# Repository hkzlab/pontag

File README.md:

# PONTAG
## Introduction
PONTAG is a board that converts a PS/2 mouse into a serial mouse that can be used on old IBM PC and clones, which lacked PS/2 ports but had plenty of serial interfaces (especially if expansion cards are installed).

## Features & Limitations
* Supports 3 buttons+wheel PS/2 mouses and converts their protocol to RS232 serial usable on old PC systems.
* The board requires an external power supply between 8V and 12V to power the MCU and mouse
* Detects PS/2 mouses with wheel and without and notifies the user via LED (5 fast blinks for a normal mouse, 20 fast blinks for a mouse with wheel)
* Can be configured for various resolutions and mouse protocols by pushing mouse buttons

### Configuration
The board can be configured during powerup by pressing the mouse keys. The configuration will be retained for all subsequent boots.
To configure the board you must keep the mouse button pressed during a reset/bootup. A sequence of **15 slow blinks** will notify the user of the accepted command, then the board will be reset with the new configuration.

* **Left mouse button pressed**: Switches between simple Microsoft protocol and Microsoft protocol with wheel (**DEFAULT:** MS+Wheel)
* **Right mouse button pressed**: Switches mouse resolution, switching between 1, 2, 4 or 8 counts per mm traveled (**DEFAULT:** 4 counts per mm)
* **Both buttons pressed**: Resets the board to defaults

### Extra Header
The board supports some special options that can be toggled via external header, shorting the corrisponding pin to GND.

* **Pin 1**: The board will enter debug mode, and start printing debug strings on the serial port. It will NOT work as a mouse.
* **Pin 2**: If jumpered, the board enter power save mode after 3 minutes of mouse inactivity.
* **Pin 3**: If shorted, forces the use of the simple Microsoft protocol (2 buttons, no wheel), regardless of what is stored in the EEPROM.
* **Pin 4**: If jumpered, the board will skip the PS/2 intellimouse wheel activation sequence. (**not exposed on board 1.0 !!!**)

## Supported protocols
PONTAG emulates a Microsoft 3-buttons Wheel serial mouse by default and transmits the `0x4D 0x5A 0x40 0x00 0x00 0x00` detection string when RTS signal is toggled.

The boards are tested with [CuteMouse](http://cutemouse.sourceforge.net/).

## Credits

- Some footprints are taken from [4x1md](https://github.com/4x1md/kicad_libraries)
- Took and modified PS/2 code from [sensi.org](http://sensi.org/~svo/%5Bm%5Douse/) and [mouse1351](https://github.com/svofski/mouse1351)

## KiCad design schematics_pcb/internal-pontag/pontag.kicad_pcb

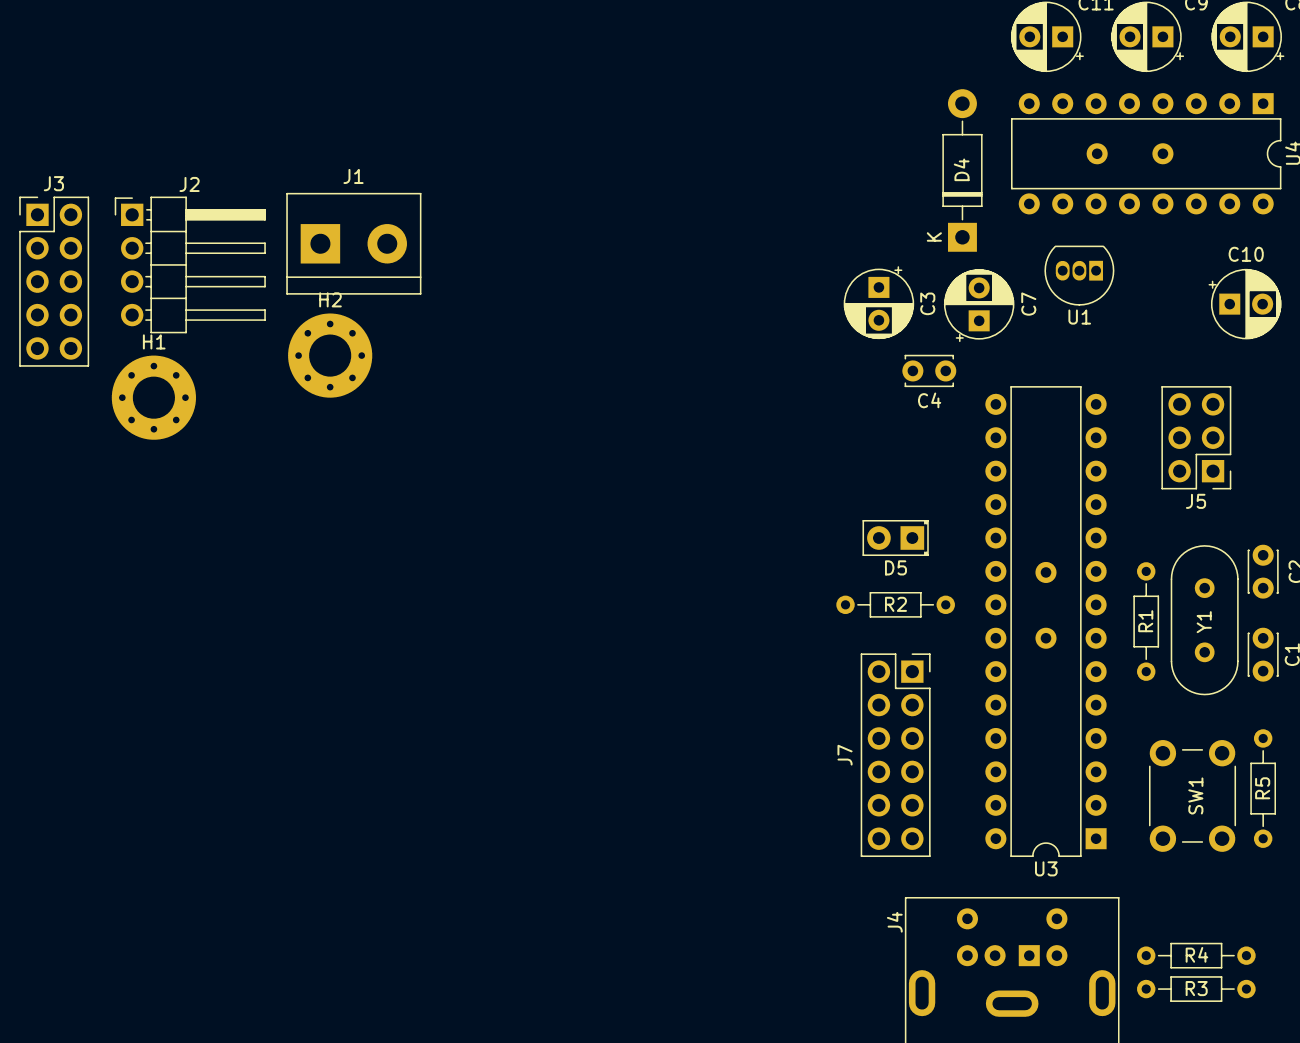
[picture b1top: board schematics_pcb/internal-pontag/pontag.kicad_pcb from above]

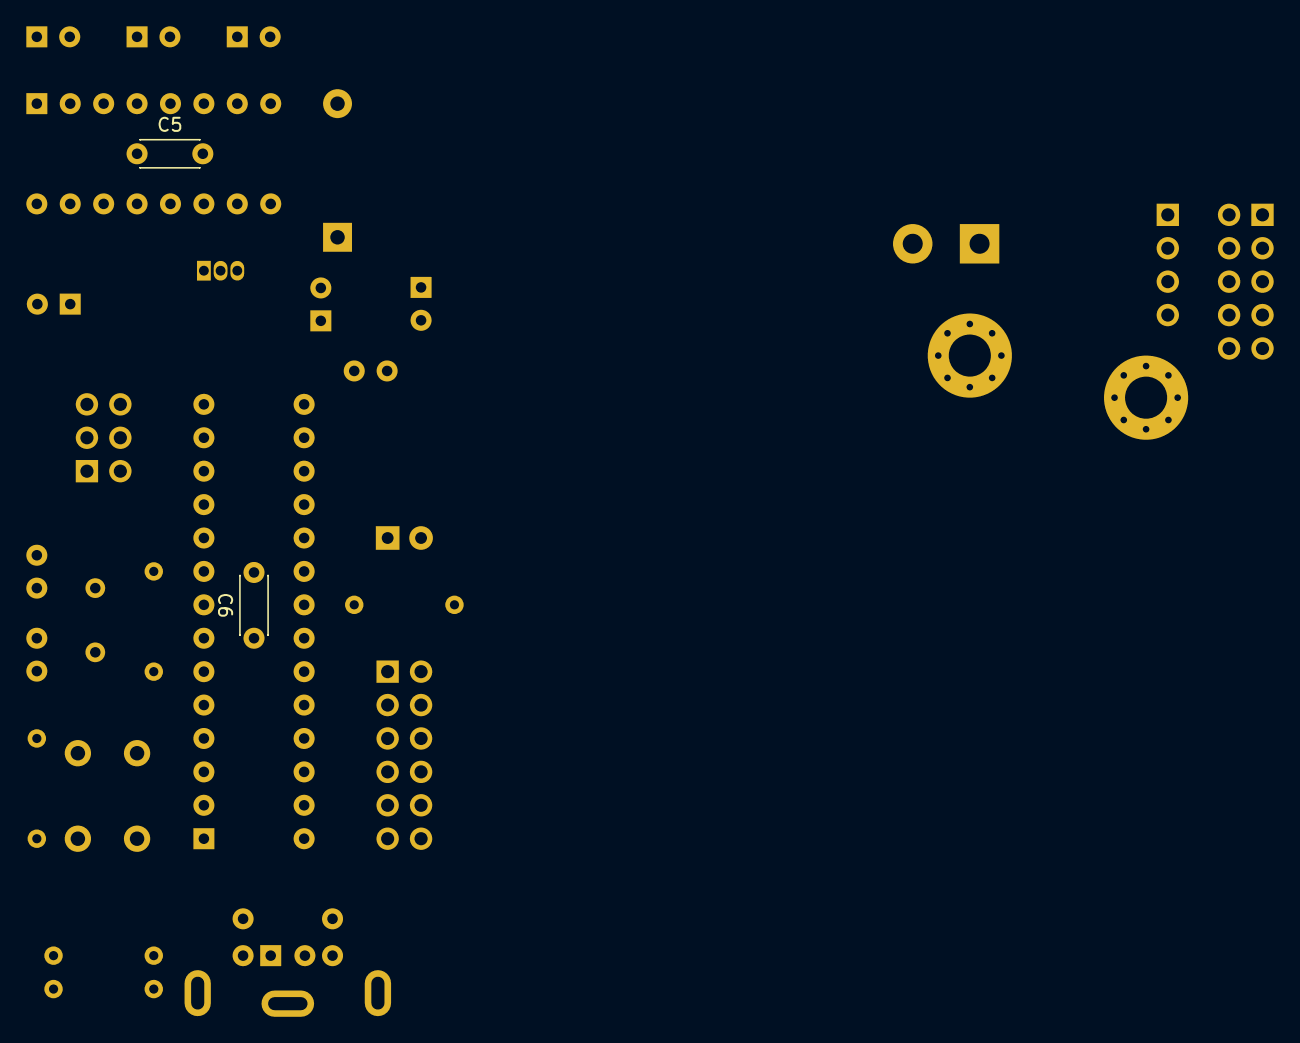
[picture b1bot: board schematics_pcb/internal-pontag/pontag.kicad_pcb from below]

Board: 2 copper layers, 31 parts (2 on the bottom side), 31 nets, no tracks yet.

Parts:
C1, C2: 22pF; C_Disc_D3.0mm_W2.0mm_P2.50mm
C3, C7, C8, C9, C10, C11: 1.0uF; CP_Radial_D5.0mm_P2.50mm
C4: 10nF; C_Disc_D3.4mm_W2.1mm_P2.50mm
C5, C6: 100nF; C_Disc_D4.3mm_W1.9mm_P5.00mm
D4: 1N4001; D_DO-41_SOD81_P10.16mm_Horizontal
D5: LED; LED_D2.0mm_W4.8mm_H2.5mm_FlatTop
H1, H2: MountingHole_Pad; MountingHole_3.2mm_M3_Pad_Via
J1: PWR Connector; TerminalBlock_bornier-2_P5.08mm
J2: Floppy PWR Connector; PinHeader_1x04_P2.54mm_Horizontal
J3: RS232 Port; PinHeader_2x05_P2.54mm_Vertical
J4: PS/2 Mouse; Connector_Mini-DIN_Female_6Pin_2rows
J5: AVR-ISP-6; PinHeader_2x03_P2.54mm_Vertical
J7: Extra; PinSocket_2x06_P2.54mm_Vertical
R1: 1M; R_Axial_DIN0204_L3.6mm_D1.6mm_P7.62mm_Horizontal
R2: 470; R_Axial_DIN0204_L3.6mm_D1.6mm_P7.62mm_Horizontal
R3, R4: 5K; R_Axial_DIN0204_L3.6mm_D1.6mm_P7.62mm_Horizontal
R5: 10K; R_Axial_DIN0204_L3.6mm_D1.6mm_P7.62mm_Horizontal
SW1: Reset; SW_PUSH_6mm
U1: L78L05_TO92; TO-92_Inline
U3: ATmega328P-PU; DIP-28_W7.62mm
U4: MAX232; DIP-16_W7.62mm
Y1: 8.0Mhz; Crystal_HC49-U_Vertical

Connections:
+12V: C3.1, D4.1, U1.3
/MISO: J5.1, U3.18
/MOSI: J5.4, U3.17
/PS2-CLOCK: J4.5, R4.2, U3.4
/PS2-DATA: J4.1, R3.2, U3.6
/RESET: J5.5, R5.1, SW1.2, U3.1
/RS232-RTS: J3.7, U4.13
/RS232-RX: J3.2, U4.7
/RS232-TX: J3.3, U4.8
/SCK: D5.2, J5.3, U3.19
/TTL-CTS: U3.5, U4.12
/TTL-RX: U3.2, U4.9
/TTL-TX: U3.3, U4.10
/XTAL1: C1.2, R1.1, U3.9, Y1.2
/XTAL2: C2.2, R1.2, U3.10, Y1.1
GND: C1.1, C2.1, C3.2, C4.2, C5.2, C6.2, C7.2, C11.1, H1.1, H2.1, J1.2, J2.2, J2.3, J3.5, J4.3, J4.7, J5.6, J7.2, J7.4, J7.6, J7.8, J7.10, J7.12, R2.2, SW1.1, U1.2, U3.8, U3.22, U4.11, U4.15
unnamed: C8.1, U4.1
unnamed: C8.2, U4.3
unnamed: C9.1, U4.4
unnamed: C9.2, U4.5
unnamed: C10.1, U4.2
unnamed: C11.2, U4.6
unnamed: D4.2, J1.1, J2.4
unnamed: D5.1, R2.1
unnamed: J7.1, U3.23
unnamed: J7.3, U3.24
unnamed: J7.5, U3.25
unnamed: J7.7, U3.26
unnamed: J7.9, U3.27
unnamed: J7.11, U3.28
VCC: C4.1, C5.1, C6.1, C7.1, C10.2, J4.4, J5.2, R3.1, R4.1, R5.2, U1.1, U3.7, U3.20, U3.21, U4.16

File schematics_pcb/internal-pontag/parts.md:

# Pontag proto 00
## Parts list
### ICs
- U1 - 78L05 TO92 regulator
- U3 - ATMega328P
- U4 - MAX232

### Resistors
- R1 - 1M ohm resistor
- R2 - 470 ohm resistor
- R3,R4 - 5K ohm resistors
- R5 - 10K ohm resistors

### Capacitors
- C1,C2 - 22pF disc ceramic capacitors
- C3,C8-C11 - 1.0uF/25V electrolytic capacitors
- C4 - 10nF ceramic capacitor
- C5,C6 - 100nF ceramic capacitors
- C7 - 1.0uF ceramic capacitor

### Diodes
- D1-D3 - 1n4148 silicon diodes
- D4 - 1n4001 diode
- D5 - LED

### Headers & Connectors
- J1 - 02x02 2.54mm header
- J2 - 01x02 2.54mm header
- J3 - DB9 female connector
- J4 - 6pin Mini-din female connector
- J5 - 02x03 2.54mm header
- J6 - 01x02 2.54mm header
- J7 - 02x06 2.54mm header
- JP1 - 01x02 2.54mm header
- JP2 - 01x02 2.54mm header

### Misc
- SW1 - 4pin push button
- Y1 - 8Mhz crystal

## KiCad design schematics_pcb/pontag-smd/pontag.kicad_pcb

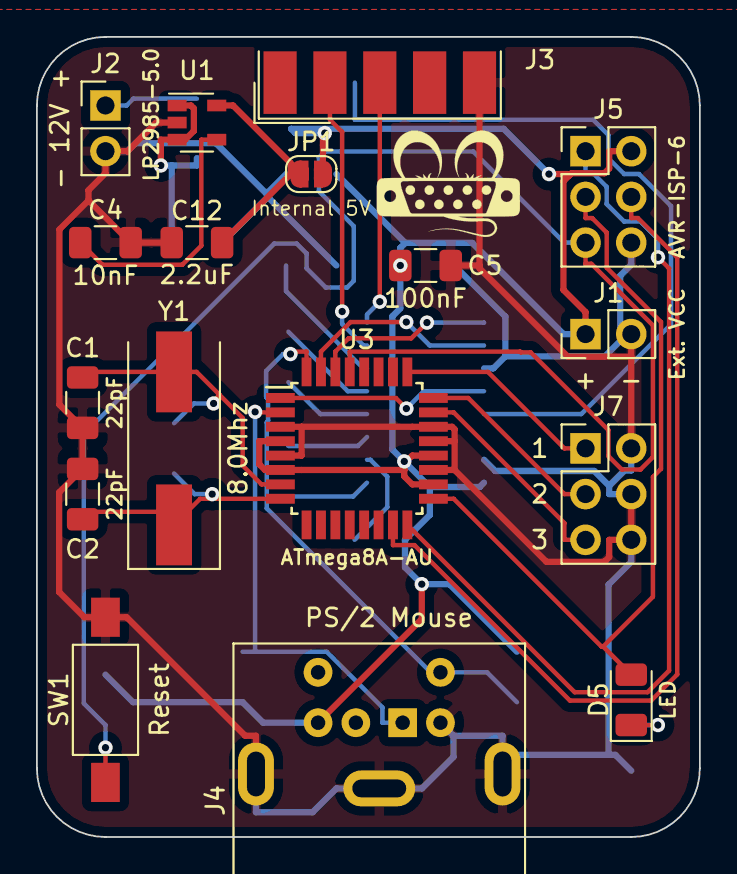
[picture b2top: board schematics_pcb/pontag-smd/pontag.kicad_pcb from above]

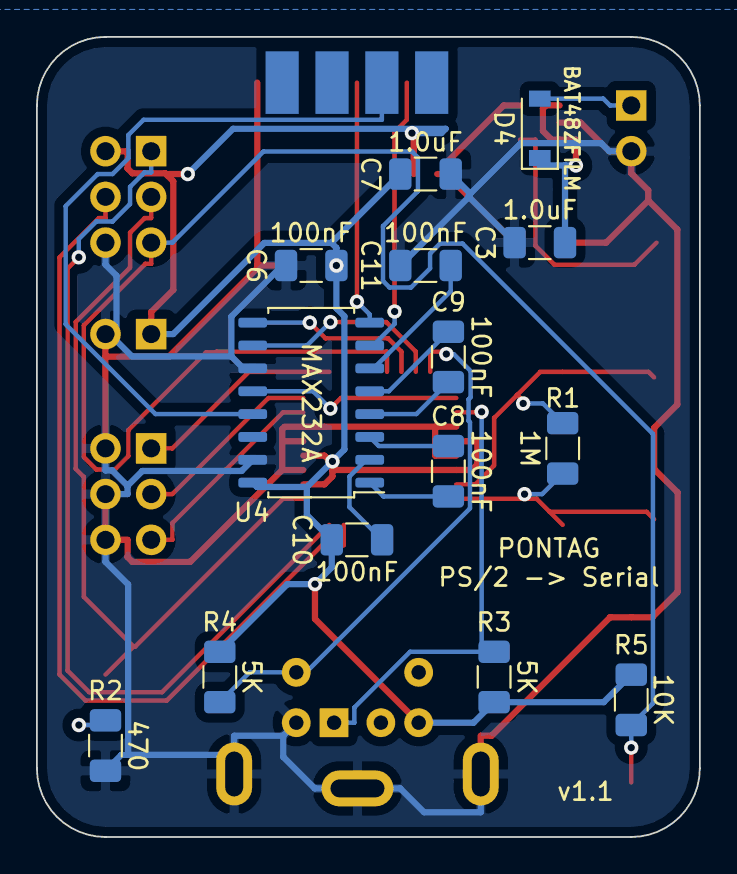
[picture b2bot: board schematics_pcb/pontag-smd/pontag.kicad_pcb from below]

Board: 2 copper layers, 36.8 x 44.5 mm, 31 parts (14 on the bottom side), 30 nets.

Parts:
C1, C2: 22pF; C_1206_3216Metric
C3, C7: 1.0uF; C_1206_3216Metric
C4: 10nF; C_1206_3216Metric
C5, C6, C8, C9, C10, C11: 100nF; C_1206_3216Metric
C12: 2.2uF; C_1206_3216Metric
D4: BAT48ZFILM; D_SOD-123
D5: LED; LED_1206_3216Metric
J1: Ext. VCC; PinHeader_1x02_P2.54mm_Vertical
J2: External 12V; PinHeader_1x02_P2.54mm_Vertical
J3: RS232 Port; DSUB-9_Female_EdgeMount_P2.77mm
J4: PS/2 Mouse; Connector_Mini-DIN_Female_6Pin_2rows
J5: AVR-ISP-6; PinHeader_2x03_P2.54mm_Vertical
J7: Extra; PinHeader_2x03_P2.54mm_Vertical
JP1: Internal 5V; SolderJumper-2_P1.3mm_Open_RoundedPad1.0x1.5mm
R1: 1M; R_1206_3216Metric
R2: 470; R_1206_3216Metric
R3, R4: 5K; R_1206_3216Metric
R5: 10K; R_1206_3216Metric
SW1: Reset; SW_SPST_FSMSM
U1: LP2985-5.0; SOT-23-5
U3: ATmega8A-AU; TQFP-32_7x7mm_P0.8mm
U4: MAX232A; SOIC-16_4.55x10.3mm_P1.27mm
Y1: 8.0Mhz; Crystal_SMD_HC49-SD

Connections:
+12V: C3.1, D4.1, U1.1, U1.3
/MISO: J5.1, U3.16
/MOSI: J5.4, U3.15
/PS2-CLOCK: J4.5, R4.2, U3.32
/PS2-DATA: J4.1, R3.2, U3.2
/REG_5V: C12.1, JP1.1, U1.5
/RESET: J5.5, R5.2, SW1.1, U3.29
/RS232-RTS: J3.7, U4.13
/RS232-RX: J3.2, U4.7
/RS232-TX: J3.3, U4.8
/SCK: D5.2, J5.3, U3.17
/TTL-CTS: U3.1, U4.12
/TTL-RX: U3.30, U4.9
/TTL-TX: U3.31, U4.10
/XTAL1: C1.2, R1.1, U3.7, Y1.2
/XTAL2: C2.2, R1.2, U3.8, Y1.1
GND: C1.1, C2.1, C3.2, C4.2, C5.2, C6.2, C7.2, C11.2, C12.2, J1.2, J2.2, J3.5, J4.3, J4.7, J5.6, J7.2, J7.4, J7.6, R2.2, SW1.2, U1.2, U3.3, U3.5, U3.19, U3.21, U3.22, U4.11, U4.15
unnamed: C4.1, U1.4
unnamed: C8.1, U4.1
unnamed: C8.2, U4.3
unnamed: C9.1, U4.4
unnamed: C9.2, U4.5
unnamed: C10.1, U4.2
unnamed: C11.1, U4.6
unnamed: D4.2, J2.1
unnamed: D5.1, R2.1
unnamed: J7.1, U3.25
unnamed: J7.3, U3.24
unnamed: J7.5, U3.23
VCC: C5.1, C6.1, C7.1, C10.2, J1.1, J4.4, J5.2, JP1.2, R3.1, R4.1, R5.1, U3.4, U3.6, U3.18, U3.20, U4.16

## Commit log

2019-12-10 First mouse doc added
2019-12-10 Fix formatting
2019-12-10 Add further documentation
2019-12-10 Add documentation
2019-12-10 Update doc
2019-12-10 Add empty project
2019-12-10 Configure for arduino
2019-12-10 Fix flashing
2019-12-11 Add PS/2 Protocol document
2019-12-11 Add datasheets
2019-12-11 Add doc about AVR
2019-12-14 Add basic PS/2 proto files
2019-12-14 Remove PS2 kbd unused code
2019-12-14 Add some comments
2019-12-16 Add PS/2 protocol
2019-12-16 Add PS/2 commands
2019-12-23 Add first code for circular buffer
2019-12-24 Fix pushData
2019-12-24 Begin adding debug code for the mouse
2019-12-24 Add struct for PS2 mouse movement
2019-12-24 Rework command transmission
2019-12-24 Take out data management from the interrupt
2019-12-27 Begin implementing the conversion
2019-12-27 add data conversion example
2020-01-03 Add support for the middle mouse button
2020-01-03 Add 'hello' serial mouse packet
2020-01-03 Begin wiring up the conversion code
2020-01-03 Add "hello" packet when INT1 toggles
2020-01-03 Change port input code
2020-01-03 Add hello delay and some comments
2020-01-03 Add max232 datasheet
2020-01-11 Fix building
2020-01-11 Another build fix
2020-01-11 Start fixing the proto
2020-01-11 Fix proto
2020-01-11 Rename function
2020-01-12 Add datasheet and add comments to main code
2020-01-12 Rename the makefile for 328p
2020-01-13 cleanup
2020-01-13 Change order of output
2020-01-14 Remove code to pilot internal pullups
2020-01-14 Fix comments
2020-01-14 Remove ATMega128 code
2020-01-14 Add mouse commands
2020-01-14 Add comments
2020-01-14 Add watchdog
2020-01-14 Use a 2 second watchdog
2020-01-14 Other cleanup
2020-01-14 blah
2020-01-14 Import PS/2 code
2020-01-14 Begin importing other code
2020-01-14 Begin porting code
2020-01-14 Begin converting some code
2020-01-15 Fix building for ATMega8A
2020-01-15 Disable code that doesn't run on 328p
2020-01-15 Disable code for attiny, fix programmer device
2020-01-15 Begin clearing TODOs
2020-01-15 Remove some TODOs related to interrupts
2020-01-15 Clear more TODOs
2020-01-15 Remove other TODOs
2020-01-15 More TODOs
2020-01-15 Remove another TODO
2020-01-15 More TODOs!
2020-01-15 Anothe TODO!
2020-01-15 Add entries in proto
2020-01-15 Begin adding mouse proto
2020-01-15 Begin preparing branch with higher level mouse code
2020-01-15 Begin adding mouse code
2020-01-15 Add more mouse code
2020-01-15 Add code to protect transmission of the HELLO message
2020-01-15 Maybe finally fix the proto?
2020-01-15 Change the defaults
2020-01-15 Increase 'M' count
2020-01-15 Change timing again
2020-01-15 Changed timing again...
2020-01-17 Add empty kicad project
2020-01-18 Begin keeping track of TODOs
2020-01-18 Add ifdefs to distinguish between 8/16 mhz in 328p
2020-01-18 Add TODOs
2020-01-18 Add initial schematics
2020-01-18 Begin creating the schematic
2020-01-18 Add 5V regulation
2020-01-18 More changes to the schematics
2020-01-18 More changes
2020-01-18 Begin wiring the MAX232
2020-01-19 Add connections to RS232 port and MAX232
2020-01-19 Additional schematics changes
2020-01-19 Begin assigning footprints
2020-01-19 Add footprint for PS/2
2020-01-19 Include necessary libraries
2020-01-19 More footprints
2020-01-19 Assigned all footprints
2020-01-19 Commit the cache files
2020-01-20 Add missing libraries
2020-01-20 Begin drawing PCB
2020-01-20 Draw the circuit for pontag
2020-01-20 Add silkscreen
2020-01-20 Fix DRC error
2020-01-25 Add gerbers
2020-02-08 Add bootloader
2020-02-08 Add parts list
2020-02-08 Fix parts list
2020-02-08 Fix define for vscode
2020-02-08 Update TODO
2020-02-10 Add new bootloader
2020-02-10 Make sure the led port is an output and off
2020-02-10 Change bootloader doc
2020-02-10 Add watchdog kick while resetting the mouse
2020-02-11 Add ATMega8 bootloader
2020-02-11 Begin fixing code for 8a
2020-02-11 Fix UART for ATMega8A
2020-02-12 Added CHANGELOG, move TODO out of the project
2020-02-12 Add additional protocol doc
2020-02-12 Send the Logitech hello packet
2020-02-12 Fix compilation
2020-02-12 Reduce the number of repetitions for the packet
2020-02-12 Update changelog
2020-02-12 Further reduce the number of packets sent as hello
2020-02-12 Change default device for 328p_8
2020-02-12 Moving around the documentation
2020-02-12 Add LED toggle when initializing the mouse
2020-02-12 Change how reset works, now correct checks result
2020-02-12 Add PS/2++ documentation
2020-02-13 Cleanup comments
2020-02-14 Add function pointers to send different detect pkts
2020-02-14 Fix libraries;
2020-02-14 Configure the option port
2020-02-14 Read options from header
2020-02-14 Begin chaning the logic that triggers sending the 4th byte
2020-02-14 Use Microsoft wheel protocol
2020-02-14 Update documentation
2020-02-14 Add sequence for magic knock
2020-02-14 Add mouse sendSequence code
2020-02-14 Invert option header check
2020-02-14 Begin adding code for PS/2++ initialization on mouse_init
2020-02-14 Add way to get info on PS/2++ from mouse init
2020-02-14 Save magic knock in program memory
2020-02-14 Send the knock sequence
2020-02-15 Fix button reading at beginning
2020-02-15 Enable wheel mode
2020-02-15 Begin adding detection of PS/2 packet sizes
2020-02-15 Set wheel movement in serial packet
2020-02-15 Add debug prints
2020-02-15 Remove useless repetition of the detect string
2020-02-15 Accept 0xFA as answer to reset, add blinking to distinguish mouse type
2020-02-15 Add empty files for permanent configuration
2020-02-15 Add code for CRC16
2020-02-15 Add structure for config saving
2020-02-15 Better naming for header config
2020-02-15 Begin adding code to read/write configuration
2020-02-15 Add eeprom read/write code
2020-02-15 Save buttons from initialization
2020-02-15 Add soft_reset code for when config changes
2020-02-15 Wire up configuration change by mouse buttons
2020-02-15 Make sure we're not going crazy because we got an 0xFA when we request a status
2020-02-15 Fix Makefile
2020-02-15 Correctly read ID even on old mouses
2020-02-15 Cleanup code a bit
2020-02-16 Add debug strings printed when enabling debug mode via header
2020-02-16 Begin changing the schematic for SMD board
2020-02-16 Begin drawing SMD board
2020-02-16 Commit cache changew
2020-02-16 Update schematics and PCB
2020-02-16 Changed some connectors
2020-02-16 Add timeouts to READID and READSTATUS functions
2020-02-16 Notify via led in case there is a detection error
2020-02-17 Add pin header to disable wheel detection
2020-02-17 Organize some components
2020-02-17 Go on with board routing
2020-02-17 Updates on SMD PCB
2020-02-17 Add silkscreen text
2020-02-17 Add logo to board
2020-02-17 Add SMD gerbers
2020-02-18 Highlight pin names in list
2020-02-19 Add logitech mouse doc
2020-03-01 fix reset packets
2020-11-01 Removed empty kicad project
2020-11-01 Add pcb picture
2020-11-01 Add board picture to README
2020-11-01 Fixed typo
2020-11-02 Added licence for the PCBs
2020-11-02 Update the README
2020-11-02 Additional description in README
2020-11-07 Give credit where credit is due!
2020-11-07 Rephrase
2020-11-07 Add github mouse1351 url
2020-11-07 Better link for mouse1351 description
2020-11-07 Add basic sleep mode code
2020-11-07 Add code to read milliseconds since start
2020-11-07 Attempt to add sleep mode to code
2020-11-08 Updated README, tweaked sleep mode to 2 minutes
2020-11-08 Update time before sleeping
2020-11-08 Update sleep time again
2020-12-02 Use the led to notify the user of the selected mouse config
2020-12-02 halve the speed of the mouse and take the overflow into consideration
2020-12-02 Remove outdated comments
2020-12-02 change what part of the PS/2 data is used to build the serial packet
2020-12-07 slightly change how the movement for the mouse is calculated
2021-06-02 Minimal changes to silkscreen
2021-06-02 Rerouted some traces
2021-08-19 Begin working on internal board
2021-08-19 Added some "not connected" points
2021-08-22 prepare files for internal PCB
2021-08-22 Use an angled reset button
